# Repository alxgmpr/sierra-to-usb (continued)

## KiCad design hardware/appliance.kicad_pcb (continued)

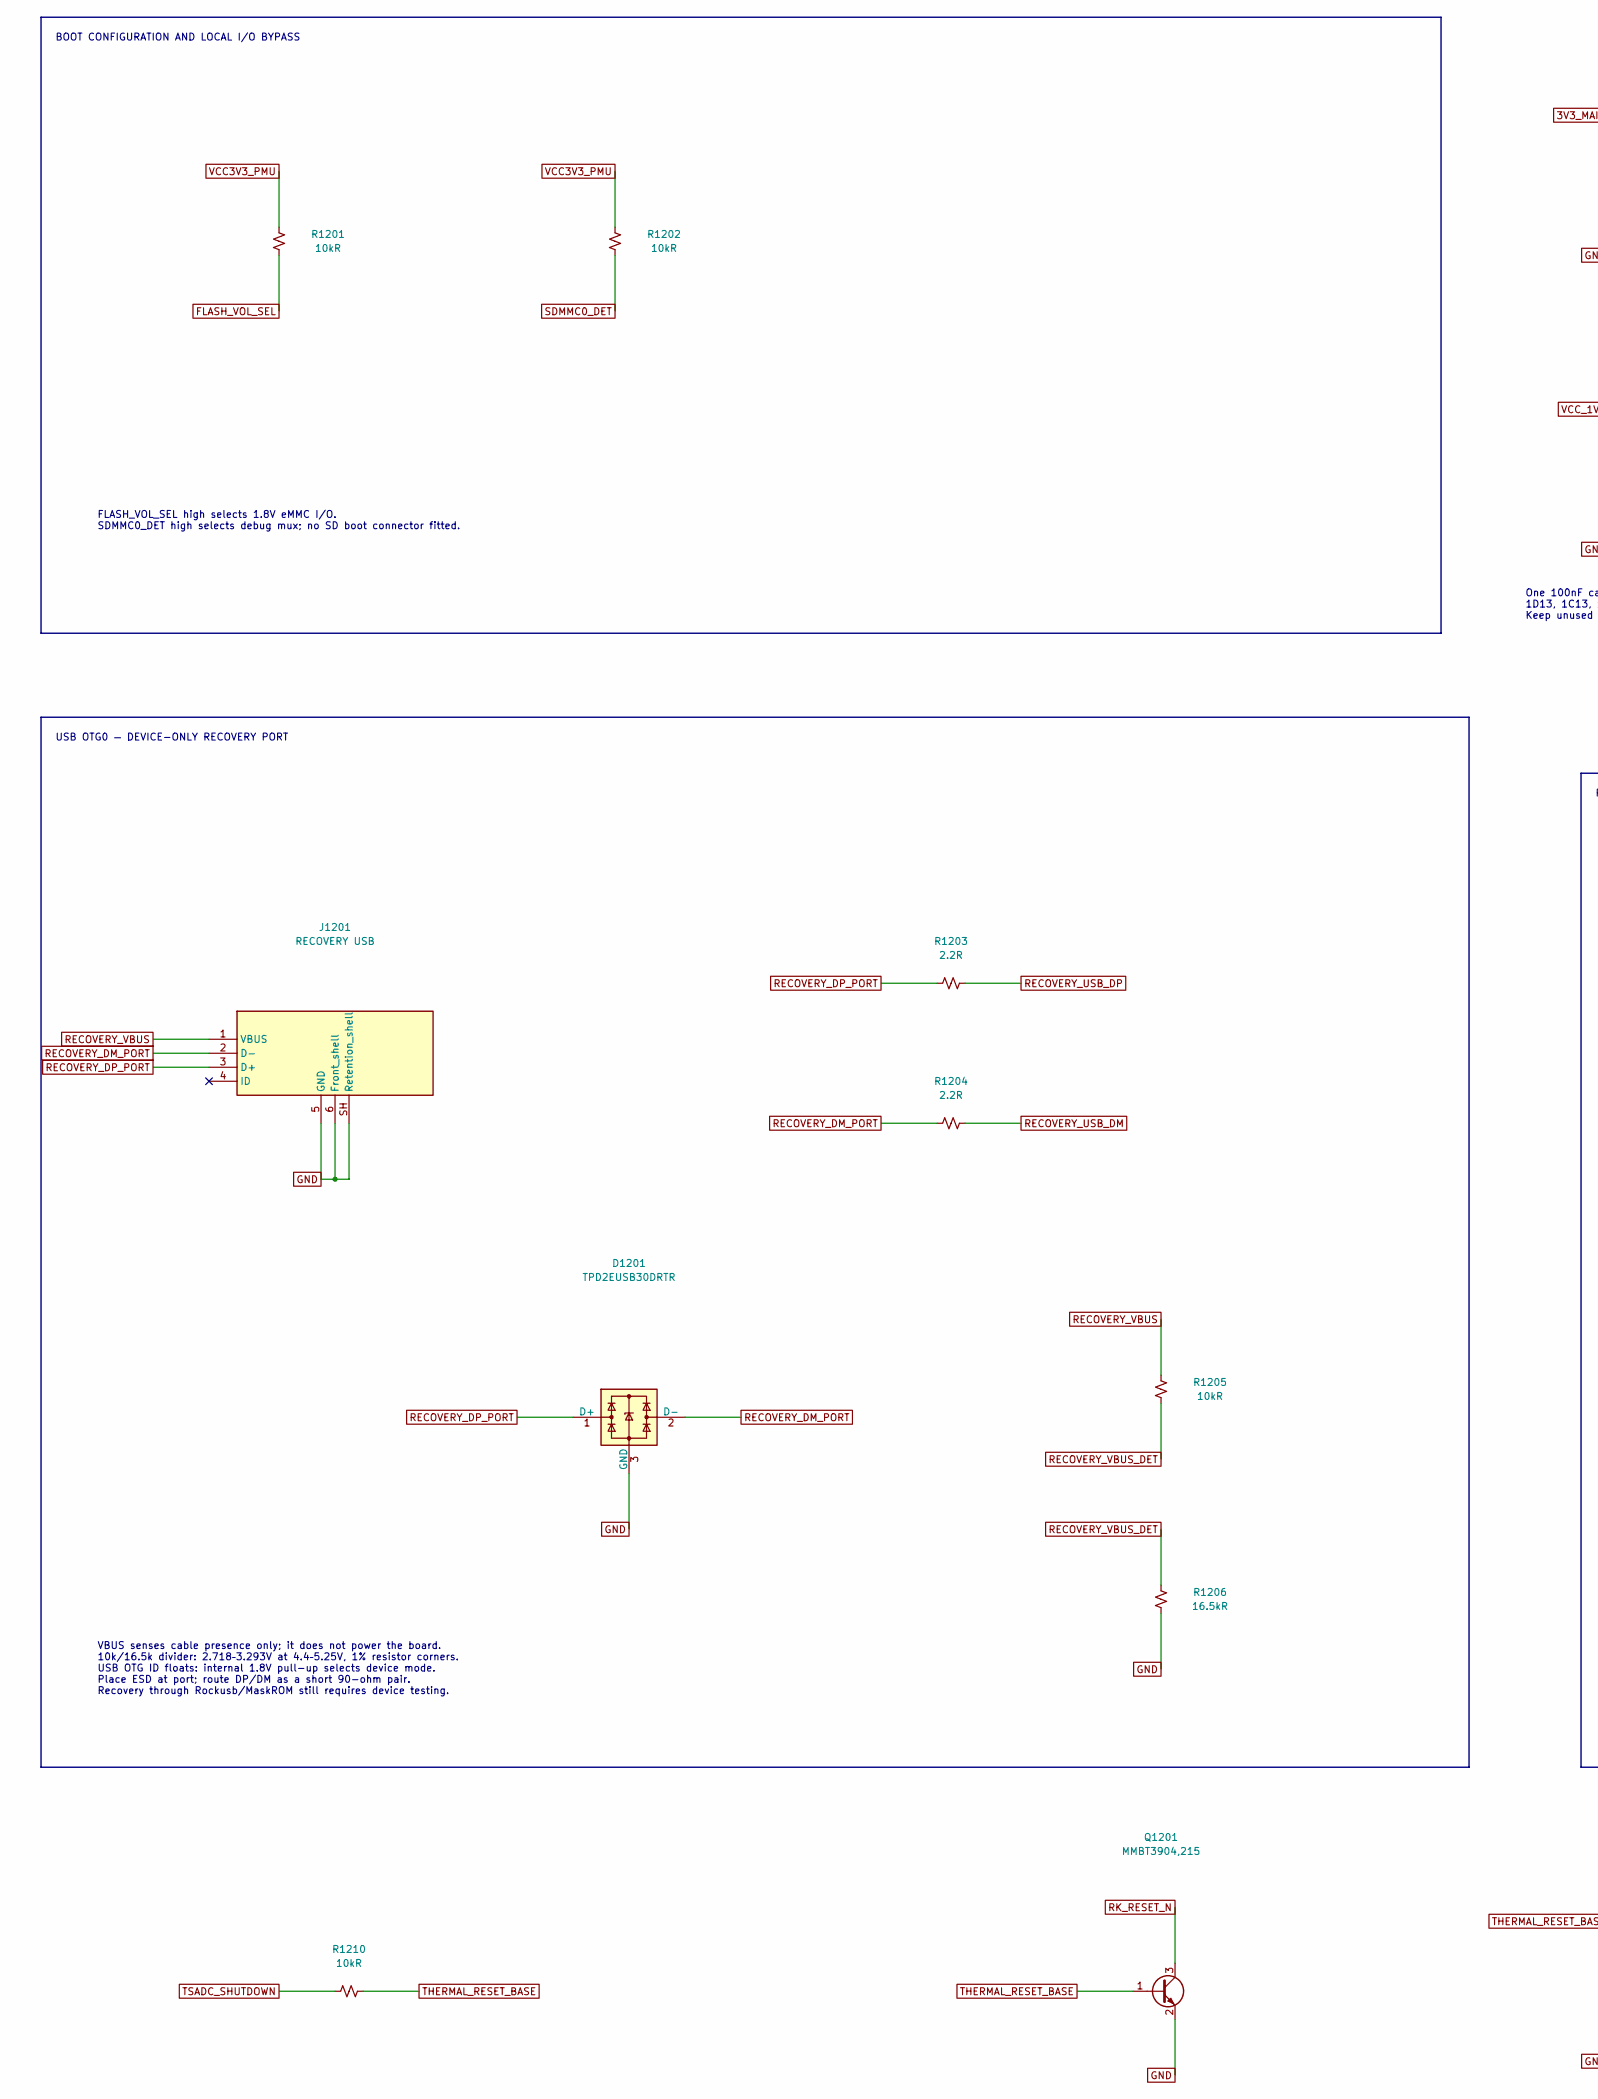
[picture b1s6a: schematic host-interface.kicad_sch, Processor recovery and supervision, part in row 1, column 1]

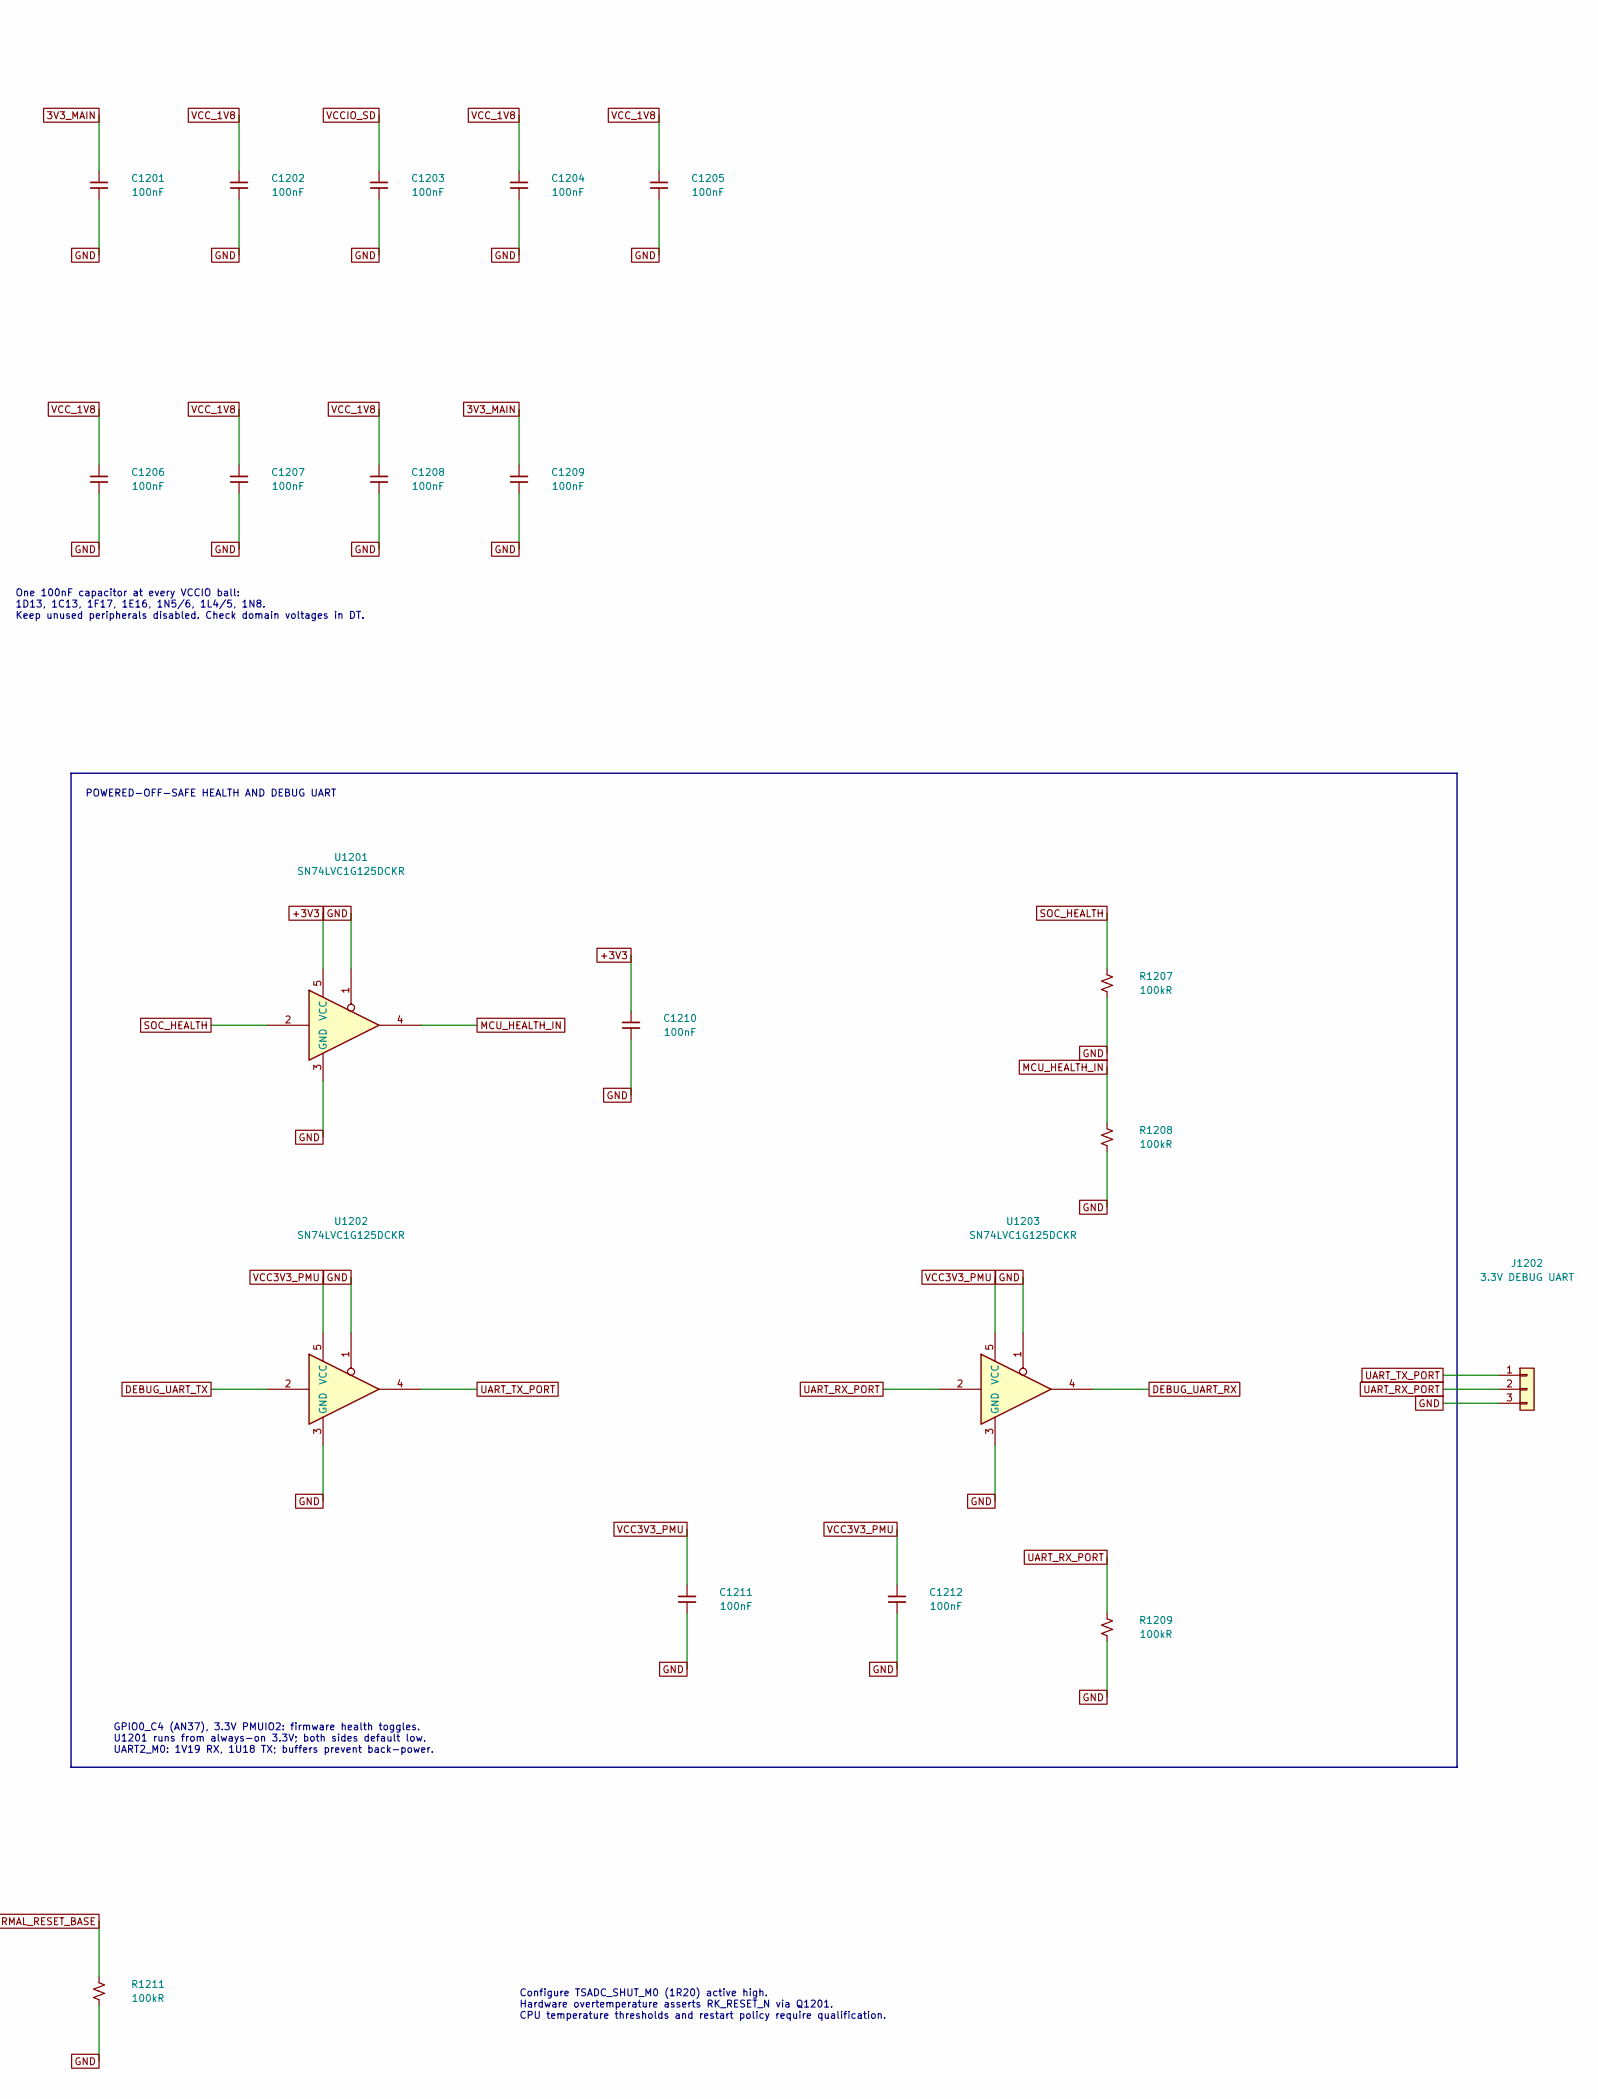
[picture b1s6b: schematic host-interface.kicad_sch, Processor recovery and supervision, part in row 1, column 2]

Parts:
C1201, C1202, C1203, C1204, C1205, C1206, C1207, C1208, C1209, C1210, C1211, C1212: 100nF; C_0603_1608Metric_Pad1.08x0.95mm_HandSolder; Voltage Rating 25V; MPN CL10B104KA8NNNC
D1201: TPD2EUSB30DRTR; Texas_DRT-3; MPN TPD2EUSB30DRTR; LCSC C97502
J1201: RECOVERY USB; USB_Micro-B_Amphenol_10103594-0001LF_Horizontal; MPN 10103594-0001LF; LCSC C428495
J1202: 3.3V DEBUG UART; PinHeader_1x03_P2.54mm_Vertical; MPN 61300311121
Q1201: MMBT3904,215; SOT-23_Handsoldering; MPN MMBT3904,215
R1201, R1202, R1205, R1210: 10kR; R_0603_1608Metric_Pad0.98x0.95mm_HandSolder; Tolerance 1%; Power Rating 0.1W; MPN RC0603FR-0710KL
R1203, R1204: 2.2R; R_0603_1608Metric_Pad0.98x0.95mm_HandSolder; Tolerance 1%; Power Rating 0.1W; MPN RC0603FR-072R2L
R1206: 16.5kR; R_0603_1608Metric_Pad0.98x0.95mm_HandSolder; Tolerance 1%; Power Rating 0.1W; MPN RC0603FR-0716K5L
R1207, R1208, R1209, R1211: 100kR; R_0603_1608Metric_Pad0.98x0.95mm_HandSolder; Tolerance 1%; Power Rating 0.1W; MPN RC0603FR-07100KL
U1201, U1202, U1203: SN74LVC1G125DCKR; SOT-353_SC-70-5; MPN SN74LVC1G125DCKR; LCSC C7833

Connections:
3V3_MAIN: C1201.1, C1209.1; also elsewhere on the board
+3V3: C1210.1, U1201.5 (VCC); also elsewhere on the board
DEBUG_UART_RX: U1203.4; also elsewhere on the board
DEBUG_UART_TX: U1202.2; also elsewhere on the board
FLASH_VOL_SEL: R1201.2; also elsewhere on the board
GND: C1201.2, C1202.2, C1203.2, C1204.2, C1205.2, C1206.2, C1207.2, C1208.2, C1209.2, C1210.2, C1211.2, C1212.2, D1201.3 (GND), J1201.5 (GND), J1201.6 (Front_shell), J1201.SH (Retention_shell), J1202.3, Q1201.2 (E), R1206.2, R1207.2, R1208.2, R1209.2, R1211.2, U1201.1, U1201.3 (GND), U1202.1, U1202.3 (GND), U1203.1, U1203.3 (GND); also elsewhere on the board
MCU_HEALTH_IN: R1208.1, U1201.4; also elsewhere on the board
RECOVERY_DM_PORT: D1201.2 (D-), J1201.2 (D-), R1204.1
RECOVERY_DP_PORT: D1201.1 (D+), J1201.3 (D+), R1203.1
RECOVERY_USB_DM: R1204.2; also elsewhere on the board
RECOVERY_USB_DP: R1203.2; also elsewhere on the board
RECOVERY_VBUS: J1201.1 (VBUS), R1205.1
RECOVERY_VBUS_DET: R1205.2, R1206.1; also elsewhere on the board
RK_RESET_N: Q1201.3 (C); also elsewhere on the board
SDMMC0_DET: R1202.2; also elsewhere on the board
SOC_HEALTH: R1207.1, U1201.2; also elsewhere on the board
THERMAL_RESET_BASE: Q1201.1 (B), R1210.2, R1211.1
TSADC_SHUTDOWN: R1210.1; also elsewhere on the board
UART_RX_PORT: J1202.2, R1209.1, U1203.2
UART_TX_PORT: J1202.1, U1202.4
VCC3V3_PMU: C1211.1, C1212.1, R1201.1, R1202.1, U1202.5 (VCC), U1203.5 (VCC); also elsewhere on the board
VCCIO_SD: C1203.1; also elsewhere on the board
VCC_1V8: C1202.1, C1204.1, C1205.1, C1206.1, C1207.1, C1208.1; also elsewhere on the board

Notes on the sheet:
VBUS senses cable presence only; it does not power the board. 10k/16.5k divider: 2.718–3.293V at 4.4–5.25V, 1% resistor corners. USB OTG ID floats: internal 1.8V pull-up selects device mode. Place ESD at port; route DP/DM as a short 90-ohm pair. Recovery through Rockusb/MaskROM still requires devic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
BOOT CONFIGURATION AND LOCAL I/O BYPASS
POWERED-OFF-SAFE HEALTH AND DEBUG UART
GPIO0_C4 (AN37), 3.3V PMUIO2: firmware health toggles. U1201 runs from always-on 3.3V; both sides default low. UART2_M0: 1V19 RX, 1U18 TX; buffers prevent back-power.
Configure TSADC_SHUT_M0 (1R20) active high. Hardware overtemperature asserts RK_RESET_N via Q1201. CPU temperature thresholds and restart policy require qualification.
One 100nF capacitor at every VCCIO ball: 1D13, 1C13, 1F17, 1E16, 1N5/6, 1L4/5, 1N8. Keep unused peripherals disabled. Check domain voltages in DT.
FLASH_VOL_SEL high selects 1.8V eMMC I/O. SDMMC0_DET high selects debug mux; no SD boot connector fitted.
USB OTG0 — DEVICE-ONLY RECOVERY PORT

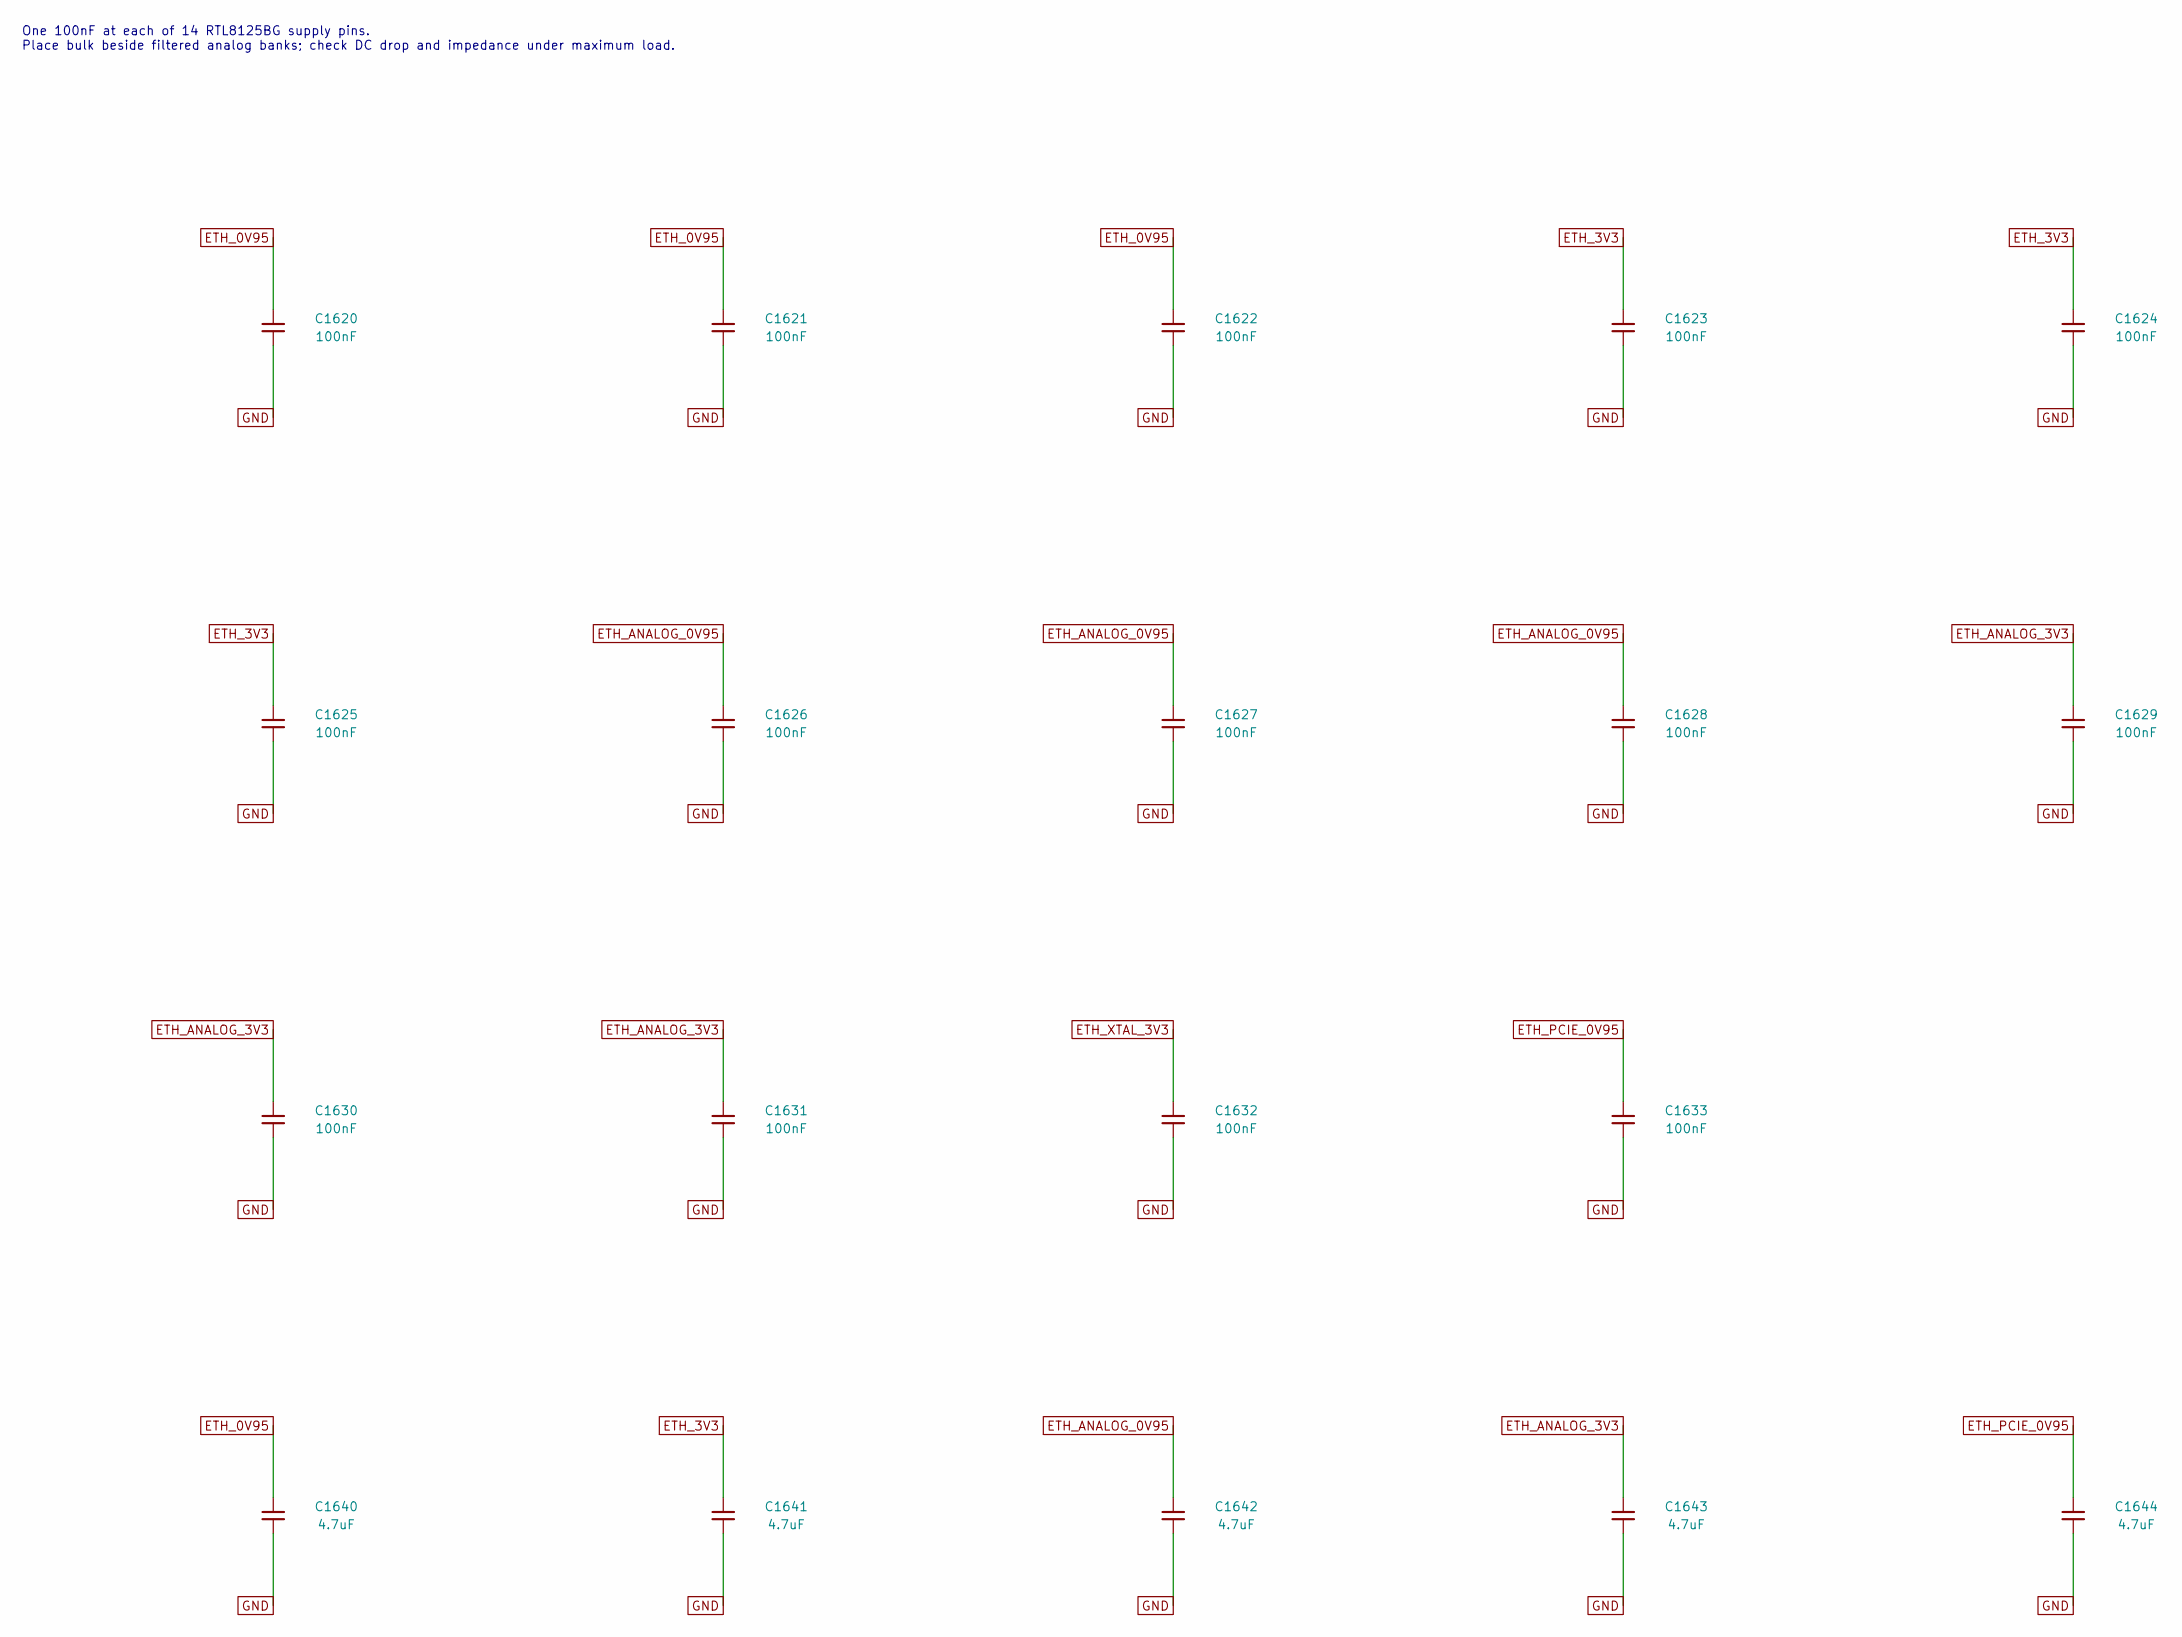
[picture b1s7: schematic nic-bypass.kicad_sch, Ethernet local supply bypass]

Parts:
C1620, C1621, C1622, C1623, C1624, C1625, C1626, C1627, C1628, C1629, C1630, C1631, C1632, C1633: 100nF; C_0603_1608Metric_Pad1.08x0.95mm_HandSolder; Voltage Rating 25V; MPN CL10B104KA8NNNC
C1640, C1641, C1642, C1643, C1644: 4.7uF; C_0603_1608Metric_Pad1.08x0.95mm_HandSolder; Voltage Rating 25V; MPN CL10A475KA8NQNC

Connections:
ETH_0V95: C1620.1, C1621.1, C1622.1, C1640.1; also elsewhere on the board
ETH_3V3: C1623.1, C1624.1, C1625.1, C1641.1; also elsewhere on the board
ETH_ANALOG_0V95: C1626.1, C1627.1, C1628.1, C1642.1; also elsewhere on the board
ETH_ANALOG_3V3: C1629.1, C1630.1, C1631.1, C1643.1; also elsewhere on the board
ETH_PCIE_0V95: C1633.1, C1644.1; also elsewhere on the board
ETH_XTAL_3V3: C1632.1; also elsewhere on the board
GND: C1620.2, C1621.2, C1622.2, C1623.2, C1624.2, C1625.2, C1626.2, C1627.2, C1628.2, C1629.2, C1630.2, C1631.2, C1632.2, C1633.2, C1640.2, C1641.2, C1642.2, C1643.2, C1644.2; also elsewhere on the board

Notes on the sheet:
One 100nF at each of 14 RTL8125BG supply pins. Place bulk beside filtered analog banks; check DC drop and impedance under maximum load.

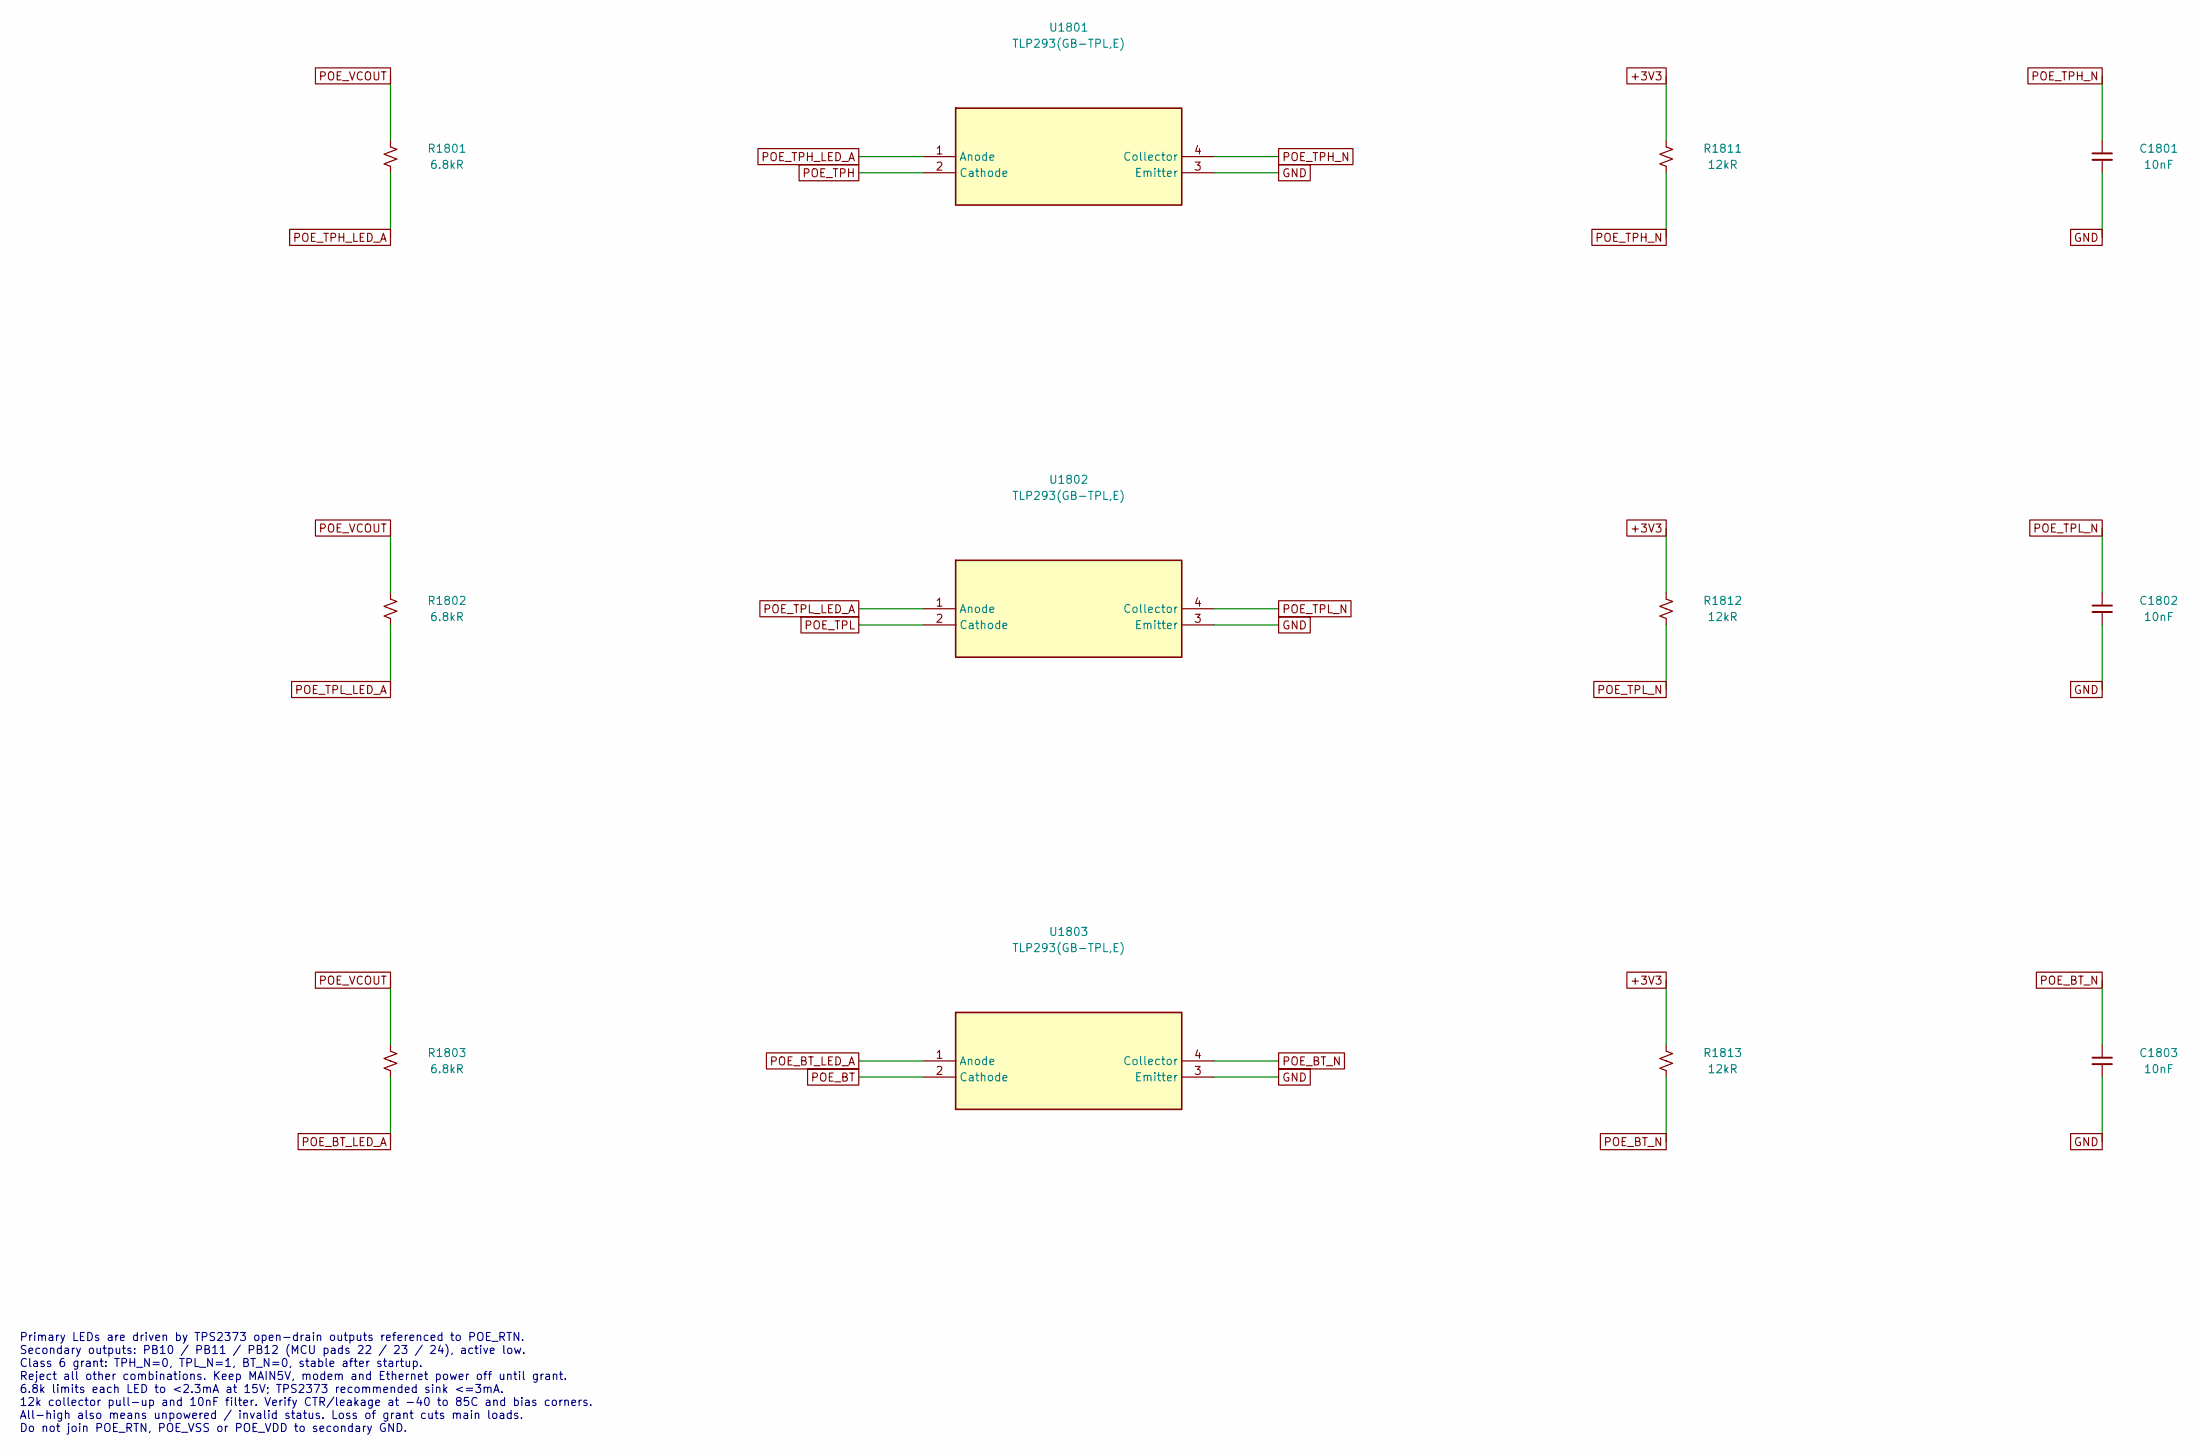
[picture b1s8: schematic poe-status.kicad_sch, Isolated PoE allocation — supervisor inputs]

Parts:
C1801, C1802, C1803: 10nF; C_0603_1608Metric_Pad1.08x0.95mm_HandSolder; Voltage Rating 50V; MPN CL10B103KB8NNNC
R1801, R1802, R1803: 6.8kR; R_0603_1608Metric_Pad0.98x0.95mm_HandSolder; Tolerance 1%; Power Rating 0.1W; MPN RC0603FR-076K8L
R1811, R1812, R1813: 12kR; R_0603_1608Metric_Pad0.98x0.95mm_HandSolder; Tolerance 1%; Power Rating 0.1W; MPN RC0603FR-0712KL
U1801, U1802, U1803: TLP293(GB-TPL,E); SOP-4_L4.4-W2.8-P1.27-LS7.0-BR; MPN TLP293(GB-TPL,E); LCSC C77656

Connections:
+3V3: R1811.1, R1812.1, R1813.1; also elsewhere on the board
GND: C1801.2, C1802.2, C1803.2, U1801.3 (Emitter), U1802.3 (Emitter), U1803.3 (Emitter); also elsewhere on the board
POE_BT: U1803.2 (Cathode); also elsewhere on the board
POE_BT_LED_A: R1803.2, U1803.1 (Anode)
POE_BT_N: C1803.1, R1813.2, U1803.4 (Collector); also elsewhere on the board
POE_TPH: U1801.2 (Cathode); also elsewhere on the board
POE_TPH_LED_A: R1801.2, U1801.1 (Anode)
POE_TPH_N: C1801.1, R1811.2, U1801.4 (Collector); also elsewhere on the board
POE_TPL: U1802.2 (Cathode); also elsewhere on the board
POE_TPL_LED_A: R1802.2, U1802.1 (Anode)
POE_TPL_N: C1802.1, R1812.2, U1802.4 (Collector); also elsewhere on the board
POE_VCOUT: R1801.1, R1802.1, R1803.1; also elsewhere on the board

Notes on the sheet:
Primary LEDs are driven by TPS2373 open-drain outputs referenced to POE_RTN. Secondary outputs: PB10 / PB11 / PB12 (MCU pads 22 / 23 / 24), active low. Class 6 grant: TPH_N=0, TPL_N=1, BT_N=0, stable after startup. Reject all other combinations. Keep MAIN5V, modem and Ethernet power off until grant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

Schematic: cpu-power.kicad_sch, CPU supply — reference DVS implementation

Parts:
C1001: 10uF; C_1206_3216Metric_Pad1.33x1.80mm_HandSolder; Voltage Rating 25V; MPN CL31B106KAHNNNE
C1002: 100nF; C_0603_1608Metric_Pad1.08x0.95mm_HandSolder; Voltage Rating 25V; MPN CL10B104KA8NNNC
C1003, C1004, C1007, C1008, C1009: 22uF; C_1210_3225Metric_Pad1.33x2.70mm_HandSolder; Voltage Rating 25V; MPN CL32B226KAJNNNE
C1005, C1006: 4.7uF; C_0603_1608Metric_Pad1.08x0.95mm_HandSolder; Voltage Rating 25V; MPN CL10A475KA8NQNC
L1001: 0.47uH; L_Coilcraft_XxL4020; MPN XGL4020-471MEC
R1001: 100kR; R_0603_1608Metric_Pad0.98x0.95mm_HandSolder; Tolerance 1%; Power Rating 0.1W; MPN RC0603FR-07100KL
U1001: TCS4525_WT; WLCSP-20_L2.0-W1.6-R5-C4-P0.40-TL; MPN TCS4525_WT; LCSC C7501359

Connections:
5V_MAIN: C1001.1, C1002.1, U1001.D1 (AVIN), U1001.D2 (PVIN), U1001.E1 (PVIN), U1001.E2 (PVIN); also elsewhere on the board
CPU_FB: U1001.A4 (FB); also elsewhere on the board
CPU_SW: L1001.1, U1001.D3 (SW), U1001.D4 (SW), U1001.E3 (SW), U1001.E4 (SW)
GND: C1001.2, C1002.2, C1003.2, C1004.2, C1005.2, C1006.2, C1007.2, C1008.2, C1009.2, R1001.2, U1001.A1 (VSEL), U1001.B2 (PGND), U1001.B3 (PGND/PG), U1001.B4 (AGND), U1001.C1 (PGND), U1001.C2 (PGND), U1001.C3 (PGND), U1001.C4 (PGND); also elsewhere on the board
PMIC_CPU_EN: R1001.1, U1001.A2 (EN); also elsewhere on the board
PMIC_I2C_SCL: U1001.A3 (SCL); also elsewhere on the board
PMIC_I2C_SDA: U1001.B1 (SDA); also elsewhere on the board
VDD_CPU: C1003.1, C1004.1, C1005.1, C1006.1, C1007.1, C1008.1, C1009.1, L1001.2; also elsewhere on the board

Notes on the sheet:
VSEL strapped low: 1.025V reset value; I2C address 0x1C. RK809 EXT_EN controls startup. Retain DVS via fan53555 driver. Five local bypass capacitors follow NanoPi R3S power sheet. Route FB separately to processor load; CPU worst-case load and current revision require closure.
CPU DYNAMIC VOLTAGE SCALING

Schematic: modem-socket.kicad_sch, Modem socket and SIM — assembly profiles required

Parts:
C2021, C2022, C2023: 10pF; C_0603_1608Metric_Pad1.08x0.95mm_HandSolder; Voltage Rating 50V; MPN CL10C100JB8NNNC
C2024: 100nF; C_0603_1608Metric_Pad1.08x0.95mm_HandSolder; Voltage Rating 25V; MPN CL10B104KA8NNNC
D2001: TPD4E02B04DQAR; USON-10_2.5x1.0mm_P0.5mm; MPN TPD4E02B04DQAR; LCSC C106794
J2001: MDT420B01411; Sierra_MDT420B01411_2x38-1MP_P0.5mm; Contact Rating 1A/power contact continuous at 25C, <=3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; MPN MDT420B01411
J2002: 1042240820; SIM-SMD_1042240820; MPN 1042240820; LCSC C585349
R2011, R2012, R2013: 0R SIERRA ONLY / DNP; R_0603_1608Metric_Pad0.98x0.95mm_HandSolder; Tolerance 5%; Power Rating 0.1W; MPN RC0603JR-070RL; not fitted
R2014, R2015: 10kR; R_0603_1608Metric_Pad0.98x0.95mm_HandSolder; Tolerance 1%; Power Rating 0.1W; MPN RC0603FR-0710KL
R2016, R2017: 0R SIERRA ONLY / DNP; R_0603_1608Metric_Pad0.98x0.95mm_HandSolder; Tolerance 5%; MPN RC0603JR-070RL; not fitted
R2018: 100kR; R_0603_1608Metric_Pad0.98x0.95mm_HandSolder; Tolerance 1%; Power Rating 0.1W; MPN RC0603FR-07100KL
R2021, R2022, R2023: 22R; R_0603_1608Metric_Pad0.98x0.95mm_HandSolder; Tolerance 1%; Power Rating 0.1W; MPN RC0603FR-0722RL
R2024: 15kR; R_0603_1608Metric_Pad0.98x0.95mm_HandSolder; Tolerance 1%; Power Rating 0.1W; MPN RC0603FR-0715KL

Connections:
GND: C2021.2, C2022.2, C2023.2, C2024.2, D2001.3 (GND), D2001.8 (GND), J2001.3 (GND), J2001.5 (GND), J2001.11 (GND), J2001.27 (GND), J2001.33 (GND), J2001.39 (GND), J2001.45 (GND), J2001.51 (GND), J2001.57 (GND), J2001.71 (GND), J2001.73 (GND), J2002.4 (GND), J2002.9 (SHELL), J2002.10 (SHELL), J2002.11 (SHELL), J2002.12 (SHELL), R2015.2; also elsewhere on the board
M2_PIN20: J2001.20 (PCIE_DIS_/_RESERVED), R2016.2
M2_PIN22: J2001.22 (VBUS_SENSE_/_RESERVED), R2017.2
M2_PIN24: J2001.24 (VCC_/_1V8_OUT), R2011.2; also elsewhere on the board
M2_PIN38: J2001.38 (VCC_/_WLAN_DISABLE), R2012.2; also elsewhere on the board
M2_PIN68: J2001.68 (VCC_/_RESERVED), R2013.2; also elsewhere on the board
MODEM_OFF_N: J2001.6 (FULL_CARD_POWER_OFF_N), R2018.2; also elsewhere on the board
MODEM_RESET_N: J2001.67 (RESET_N); also elsewhere on the board
MODEM_RXN_PORT: J2001.35 (USB_RXN); also elsewhere on the board
MODEM_RXP_PORT: J2001.37 (USB_RXP); also elsewhere on the board
MODEM_TXN_PORT: J2001.29 (USB_TXN); also elsewhere on the board
MODEM_TXP_PORT: J2001.31 (USB_TXP); also elsewhere on the board
MODEM_USB_DM_PORT: J2001.9 (USB_DM); also elsewhere on the board
MODEM_USB_DP_PORT: J2001.7 (USB_DP); also elsewhere on the board
MODEM_VCC: J2001.2 (VCC), J2001.4 (VCC), J2001.70 (VCC), J2001.72 (VCC), J2001.74 (VCC), R2011.1, R2012.1, R2013.1, R2014.1, R2017.1, R2018.1; also elsewhere on the board
SIERRA_USB_SELECT_1V8: R2014.2, R2015.1, R2016.1
SIM1_CLK: C2022.1, D2001.2 (IO2), J2002.3 (CLK), R2022.2
SIM1_CLK_MODEM: J2001.32 (SIM1_CLK), R2022.1
SIM1_DATA: C2023.1, D2001.4 (IO3), J2002.6 (I/O), R2023.2, R2024.2
SIM1_DATA_MODEM: J2001.34 (SIM1_DATA), R2023.1
SIM1_RESET: C2021.1, D2001.1 (IO1), J2002.2 (RST), R2021.2
SIM1_RESET_MODEM: J2001.30 (SIM1_RESET), R2021.1
SIM1_VCC: C2024.1, D2001.5 (IO4), J2001.36 (SIM1_VCC), J2002.1 (VCC), R2024.1

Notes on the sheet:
SIM routing <=200mm and away from RF/SW; 22R/10pF and 15k follow RM520 reference. Disable AT+QSIMDET; keep modem SIM-detect contact 66 open. Sierra open means card present. Validate SIM ATR/retry behavior with card present/absent and each profile.
Default assembly: R2011/12/13/16/17 DNP (Quectel). NEVER feed Quectel pins 24,38,68. Sierra USB profile: fit all five links; pins 24/38/68 add VCC, 20 selects USB, 22 detects VBUS. Pin 20 divider is powered by modem VCC; include module pulldown in level verification. RESET uses module internal 1.8V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

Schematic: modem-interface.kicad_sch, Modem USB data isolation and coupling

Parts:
C2001, C2002, C2003, C2004, C2005: 100nF; C_0603_1608Metric_Pad1.08x0.95mm_HandSolder; Voltage Rating 25V; MPN CL10B104KA8NNNC
Q2001: MMBT3904,215; SOT-23_Handsoldering; MPN MMBT3904,215
R2001, R2003: 10kR; R_0603_1608Metric_Pad0.98x0.95mm_HandSolder; Tolerance 1%; Power Rating 0.1W; MPN RC0603FR-0710KL
R2002: 100kR; R_0603_1608Metric_Pad0.98x0.95mm_HandSolder; Tolerance 1%; Power Rating 0.1W; MPN RC0603FR-07100KL
U2001: TMUXHS4212IRKSR; DHVQFN-20-1EP_2.5x4.5mm_P0.5mm_EP1x3mm; MPN TMUXHS4212IRKSR; LCSC C3656912
U2002: TS3USB221ARSER; UQFN-10_L2.0-W1.5-P0.50-BL; MPN TS3USB221ARSER; LCSC C128396
U2003: SN74LVC1G08DCKR; SOT-353_SC-70-5; MPN SN74LVC1G08DCKR; LCSC C7832

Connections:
+3V3: C2003.1, C2004.1, C2005.1, R2003.1, U2001.1 (RSVD1), U2001.6 (VCC), U2001.10 (RSVD2), U2002.10 (VCC), U2003.5 (VCC); also elsewhere on the board
GND: C2003.2, C2004.2, C2005.2, Q2001.2 (E), R2002.2, U2001.5 (GND), U2001.9 (SEL), U2001.11 (GND), U2001.20 (GND), U2001.21 (EP), U2002.5 (GND), U2002.9 (S), U2003.3 (GND); also elsewhere on the board
MAIN3V3_GOOD: U2003.1 (A); also elsewhere on the board
MODEM_RAIL_GOOD: U2003.2 (B); also elsewhere on the board
MODEM_RXN_PORT: U2001.18 (B0N); also elsewhere on the board
MODEM_RXP_PORT: U2001.19 (B0P); also elsewhere on the board
MODEM_TXN_AC: C2002.2, U2001.4 (A0n)
MODEM_TXN_PORT: U2001.16 (B1N); also elsewhere on the board
MODEM_TXP_AC: C2001.2, U2001.3 (A0p)
MODEM_TXP_PORT: U2001.17 (B1P); also elsewhere on the board
MODEM_USB_BASE: Q2001.1 (B), R2001.2, R2002.1
MODEM_USB_DM: U2002.7 (D-); also elsewhere on the board
MODEM_USB_DM_PORT: U2002.2 (1D-); also elsewhere on the board
MODEM_USB_DP: U2002.8 (D+); also elsewhere on the board
MODEM_USB_DP_PORT: U2002.1 (1D+); also elsewhere on the board
MODEM_USB_OE_N: Q2001.3 (C), R2003.2, U2001.2 (OEn), U2002.6 (~OE)
MODEM_USB_RXN: U2001.8 (A1n); also elsewhere on the board
MODEM_USB_RXP: U2001.7 (A1p); also elsewhere on the board
MODEM_USB_TXN_SOC: C2002.1; also elsewhere on the board
MODEM_USB_TXP_SOC: C2001.1; also elsewhere on the board
MODEM_USB_VALID: R2001.1, U2003.4 (Y)

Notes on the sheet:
Both USB muxes remain powered when modem/SoC are off. Hardware AND requires valid host and delayed modem rails before enabling data. U1903 releases after 180–420ms of valid VCC. Host TX -> module RX (37P/35N). Module TX (31P/29N) -> host RX. Module contains TX capacitors. No M.2 PCIe routing: dedic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

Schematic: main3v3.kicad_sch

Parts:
C601, C602, C603: 22uF / 25V; C_1210_3225Metric_Pad1.33x2.70mm_HandSolder; MPN CL32B226KAJNNNE; LCSC C309062
C604: 100nF / 25V; C_0603_1608Metric_Pad1.08x0.95mm_HandSolder; MPN CL10B104KA8NNNC; LCSC C1590
L601: 1uH; L_Coilcraft_XxL4030; MPN XGL4030-102MEC; LCSC C6336766
R601: 200kR; R_0603_1608Metric_Pad0.98x0.95mm_HandSolder; Tolerance 0.1%; MPN RT0603BRD07200KL; LCSC C728585
R602: 44.2kR; R_0603_1608Metric_Pad0.98x0.95mm_HandSolder; Tolerance 0.1%; MPN RT0603BRD0744K2L; LCSC C861410
R603: 20kR; R_0603_1608Metric_Pad0.98x0.95mm_HandSolder; Tolerance 1%; MPN RC0603FR-0720KL; LCSC C105575
R604, R605: 10kR; R_0603_1608Metric_Pad0.98x0.95mm_HandSolder; Tolerance 1%; MPN RC0603FR-0710KL; LCSC C98220
R606: 100kR; R_0603_1608Metric_Pad0.98x0.95mm_HandSolder; Tolerance 1%; MPN RC0603FR-07100KL; LCSC C14675
U601: MP2143DJ-LF-Z; TSOT-23-8_HandSoldering; MPN MP2143DJ-LF-Z; LCSC C43427
U602: SN74LVC1G17DBVR; SOT-23-5_HandSoldering; MPN SN74LVC1G17DBVR; LCSC C7836

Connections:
3V3_MAIN: C602.1, C603.1, L601.2, R601.1, U601.5 (OUT); also elsewhere on the board
5V_MAIN: C601.1, R603.1, R605.1, U601.2 (VIN); also elsewhere on the board
+3V3: C604.1, U602.5 (VCC); also elsewhere on the board
/Main 3.3V/MAIN3V3_EN: R603.2, R604.1, U601.8 (EN)
/Main 3.3V/MAIN3V3_FB: R601.2, R602.1, U601.7 (FB)
/Main 3.3V/MAIN3V3_PG_5V: R605.2, R606.1, U601.1 (PG), U602.2
GND: C601.2, C602.2, C603.2, C604.2, R602.2, R604.2, R606.2, U601.4 (PGND), U601.6 (AGND), U602.3 (GND); also elsewhere on the board
MAIN3V3_GOOD: U602.4; also elsewhere on the board
unnamed: L601.1, U601.3 (SW)

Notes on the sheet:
Main sequencing and PG translation captured; capacitance and thermal margins unqualified.

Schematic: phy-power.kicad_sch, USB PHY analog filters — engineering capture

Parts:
C813, C814: 1uF / 25V; C_0603_1608Metric_Pad1.08x0.95mm_HandSolder; MPN CL10B105KA8NNNC; LCSC C29936
FB801, FB802: 120R @ 100MHz; L_0603_1608Metric_Pad1.05x0.95mm_HandSolder; Current Rating 2A; MPN MPZ1608S121ATAH0; LCSC C114770

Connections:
GND: C813.2, C814.2; also elsewhere on the board
USB_AVDD_0V9: FB801.2; also elsewhere on the board
USB_AVDD_1V8: FB802.2; also elsewhere on the board
VCCA_1V8: C814.1, FB802.1; also elsewhere on the board
VDDA_0V9: C813.1, FB801.1; also elsewhere on the board

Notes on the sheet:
USB ANALOG FILTERS: local pin bypass and processor loads are captured. 45mOhm maximum DCR differs from 30mOhm reference example. Rail headroom, thermal limits and bead/capacitor damping remain to verify.
